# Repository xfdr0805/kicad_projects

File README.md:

# kicad_projects
kicad_projects

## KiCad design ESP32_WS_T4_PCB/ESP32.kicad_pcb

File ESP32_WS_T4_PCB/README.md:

# ESP32_WS_T4_PCB
2021.07.07 从LCEDA导出，放弃LCEDA

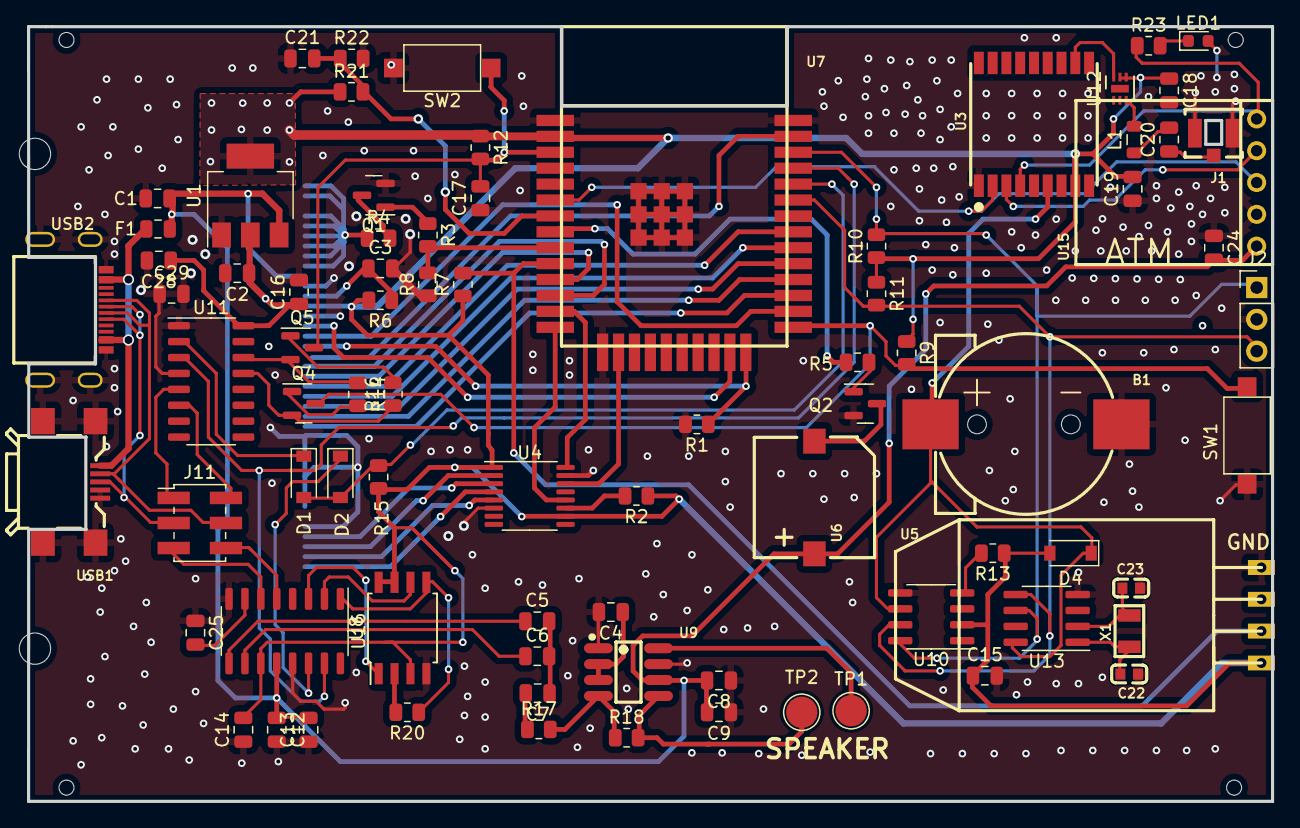
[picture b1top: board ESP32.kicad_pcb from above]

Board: 2 copper layers, 99.3 x 61.8 mm, 83 parts (0 on the bottom side), 76 nets.

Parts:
B1: CR1220-2; BAT-SMD_CR1220-2
C1, C2, C3, C9: 10uF; C_0805_2012Metric
C4, C5, C6, C8, C12, C14, C15, C17, C25, C28: 1uF; C_0805_2012Metric
C7: 0.15uF; C_0805_2012Metric
C13, C16, C18, C19, C24, C29: 0.1uF; C_0805_2012Metric
C20: 100pF; C_0805_2012Metric
C21: 100nF; C_0805_2012Metric
C22, C23: 22pF; C0603
D1, D2, D4: 1N4148WT1G; D_SOD-123
F1: 5V 500mA; Fuse_0805_2012Metric
J1: ANT; IPEX
J2: I2C; PinHeader_1x03_P2.54mm_Vertical
J11: 2mm_2x3; PinHeader_2x03_P2.00mm_Vertical_SMD
L1: 6.8nH; L_0805_2012Metric
LED1: led Green; LED_0603_1608Metric
Q1, Q2, Q4, Q5: S8050; SOT-23
R1, R2, R3, R5, R7, R8, R9, R10, R11, R21, R22: 4.7k; R_0805_2012Metric
R4: 0; R_0805_2012Metric
R6, R12, R13, R14, R16, R17: 10k; R_0805_2012Metric
R15, R23: 1k; R_0805_2012Metric
R18: 33k; R_0805_2012Metric
R20: 100; R_0805_2012Metric
SW1: Download; SW_SPST_CK_RS282G05A3
SW2: Reset; SW_SPST_CK_RS282G05A3
TFT1: TFT_39Pin_4.0; TFT_39PIN_4.0
TP1: TestPoint; TestPoint_Pad_D2.5mm
TP2: SPEAKER; TestPoint_Pad_D2.5mm
U1: UOT; SOT-223
U3: ATGM336H-5N31; GPSM-SMD_ATGM336H
U4: XPT2046; TSSOP-16_4.4x5mm_P0.65mm
U5: GND; DHT22_AM2303
U6: 无源蜂鸣器; BUZ-SMD_2PIN_FST-9650B-5V
U7: 32D; ESP32-WROOM-32D
U8: GD25Q32CSIG; SOIC-8W_5.3x5.3mm_P1.27mm
U9: 8002A; SOP8150MIL-LJN
U10: DS3231MZ+; SOIC-8_3.9x4.9mm_P1.27mm
U11: CH340C; SO-16_3.9x9.9mm_P1.27mm
U12: AT2659; DFN-6-1EP_2x2mm_P0.5mm_EP0.61x1.42mm
U13: PCF8563T/5,518; SOIC-8_3.9x4.9mm_P1.27mm
U15: ATM; GOOUUU-GPS+BD
U16: BY5301; SO-16_3.9x9.9mm_P1.27mm
USB1: MICRO CBJB1.17-4P; MICRO-USB
USB2: TYPE-C-31-M-13; USB-C-SMD_TYPE-C-31-M-13
X1: 32.768KHz; OSC-SMD_L3.2-W1.5

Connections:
+3V3: C2.1, C14.2, C15.1, C16.1, C18.1, C19.2, C28.1, D4.2 (A), R2.1, R6.2, R7.1, R9.1, R10.1, R11.1, R12.1, R13.1, R15.1, R21.1, TFT1.27 (VCC), U1.2 (OUT), U1.4 (1), U3.8 (VCC), U4.1 (VCC), U4.10 (IOVDD), U5.1, U7.2 (3V3), U8.3 (WP#), U8.7 (HOLD#), U8.8 (VCC), U10.2 (VCC), U11.16 (VCC), U12.4 (VDD), U12.5 (/SHDN), U16.11 (V3V)
/1PPS: R23.1, U3.4 (1PPS), U15.5 (PPS)
/ADC1_CH7: C21.2, R21.2, R22.1, U7.7 (IO35)
/BEEP: R5.2, U7.8 (IO32)
/CH340_RX: U7.35 (TXD0), U11.3 (RXD), U16.15 (RX)
/CH340_TX: D1.1 (K), U11.2 (TXD)
/DAC_L: C5.1, U16.9 (DACL)
/DAC_R: C6.1, U16.10 (DACR)
/DHT_DATA: R7.2, U5.2, U7.10 (IO25)
/EN: C17.2, Q5.3 (C), R12.2, SW2.1, U7.3 (EN)
/ESP32_RX: D1.2 (A), D2.2 (A), R15.2, U7.34 (RXD0)
/GPIO_0: Q4.3 (C), R9.2, SW1.1, U7.25 (IO0)
/GPS_RX: U3.3 (RXD), U15.4 (RXD)
/GPS_TX: U3.2 (TXD), U7.6 (IO34), U15.3 (TXD)
/IRQ: R2.2, U4.11 (PENIRQ#)
/SCL: J2.1, R10.2, U7.36 (IO22), U10.8 (SCL), U13.6 (SCL)
/SDA: J2.3, R11.2, U7.33 (IO21), U10.7 (SDA), U13.5 (SDA)
/TFT_BL: R3.2, R8.2, U7.9 (IO33)
/TFT_D0: TFT1.22 (DB0), U7.37 (IO23)
/TFT_D1: TFT1.21 (DB1), U7.12 (IO27)
/TFT_D2: TFT1.20 (DB2), U7.11 (IO26)
/TFT_D3: TFT1.19 (DB3), U7.31 (IO19)
/TFT_D4: TFT1.18 (DB4), U7.30 (IO18)
/TFT_D5: TFT1.17 (DB5), U7.29 (IO5)
/TFT_D6: TFT1.16 (DB6), U7.28 (IO17)
/TFT_D7: TFT1.15 (DB7), U7.27 (IO16)
/TFT_DC: TFT1.25 (RS), U7.23 (IO15)
/TFT_RD: R1.1, TFT1.23 (RD), U7.24 (IO2)
/TFT_WR: TFT1.24 (WR), U7.26 (IO4)
/TOUCH_MISO: U4.12 (DOUT), U7.14 (IO12)
/TOUCH_MOSI: U4.14 (DIN), U7.16 (IO13)
/TOUCH_SCK: U4.16 (DCLK), U7.13 (IO14)
/USB_DM: J11.6, U16.5 (DM)
/USB_DP: J11.5, U16.6 (DP)
/V-BAT: B1.1, D4.1 (K), U3.6 (VBAT), U10.6 (VBAT), U13.8 (VDD)
/VCC_5V: C1.1, C8.2, C9.2, C12.1, C13.2, C24.2, F1.2, TFT1.30 (A), U1.3 (IN), U6.1 (+), U9.6 (VDD), U15.1 (VCC), U16.12 (DC5V)
/VOICE_CS: U8.1 (CS#), U16.3 (SPI_CS)
/VOICE_DO: R20.1, U8.5 (SI), U16.1 (SPI_DO)
/VOICE_SCK: U8.6 (SCLK), U16.2 (SPI_CLK)
/VOICE_TX: D2.1 (K), U16.14 (TX)
/X+: TFT1.3 (XR), U4.2 (XP)
/X-: TFT1.1 (XL), U4.4 (XN)
/Y+: TFT1.4 (YD), U4.3 (YP)
/Y-: TFT1.2 (YU), U4.5 (YN)
GND: B1.2, C1.2, C2.2, C3.2, C4.2, C8.1, C9.1, C12.2, C13.1, C14.1, C15.2, C16.2, C17.1, C18.2, C19.1, C21.1, C22.2, C23.2, C24.1, C25.1, C28.2, C29.1, C29.2, J1.2, J1.3, J2.2, LED1.2 (K), Q1.2 (E), Q2.2 (E), R1.2, R8.1, R22.2, SW1.2, SW2.2, TFT1.5 (GND), TFT1.7 (DB15), TFT1.8 (DB14), TFT1.9 (DB13), TFT1.10 (DB12), TFT1.11 (DB11), TFT1.12 (DB10), TFT1.13 (DB9), TFT1.14 (DB8), TFT1.26 (CS), TFT1.29 (GND), U1.1 (GND), U3.1 (GND), U4.6 (GND), U4.15 (CS#), U5.4, U7.1 (GND), U7.15 (GND), U7.38 (GND), U7.39 (GND), U8.4 (VSS), U9.1 (SHUTDOWN), U9.7 (GND), U10.5 (GND), U11.1 (GND), U12.1 (GND), U12.2 (GND), U13.4 (VSS), U15.2 (GND), U16.8 (GND), U16.13 (GND), USB1.4 (ID), USB1.5 (GND), USB1.6 (EH), USB2.0 (EP), USB2.A1 (GND), USB2.A12 (GND), USB2.B1 (GND), USB2.B12 (GND)
unnamed: C3.1, R6.1, TFT1.28 (RST)
unnamed: C4.1, U9.2 (BYPASS), U9.3 (+IN)
unnamed: C5.2, C6.2, C7.1
unnamed: C7.2, R17.1
unnamed: C20.1, J1.1
unnamed: C20.2, L1.1
unnamed: C22.1, U13.1 (OSCI), X1.2 (OSC2)
unnamed: C23.1, U13.2 (OSCO), X1.1 (OSC1)
unnamed: C25.2, U16.7 (VPN)
unnamed: F1.1, USB1.1 (VCC), USB2.A4 (VBUS), USB2.A9 (VBUS), USB2.B4 (VBUS), USB2.B9 (VBUS)
unnamed: J11.1, U11.5 (D+)
unnamed: J11.2, U11.6 (D-)
unnamed: J11.3, USB1.3 (D+), USB2.A6 (DP1), USB2.B6 (DP2)
unnamed: J11.4, USB1.2 (D-), USB2.A7 (DN1), USB2.B7 (DN2)
unnamed: L1.2, U12.3 (RFIN)
unnamed: LED1.1 (A), R23.2
unnamed: Q1.1 (B), R3.1
unnamed: Q1.3 (C), R4.2
unnamed: Q2.1 (B), R5.1
unnamed: Q2.3 (C), U6.2 (-)
unnamed: Q4.1 (B), R14.2
unnamed: Q4.2 (E), R16.1, U11.13 (DTR#)
unnamed: Q5.1 (B), R16.2
unnamed: Q5.2 (E), R14.1, U11.14 (RTS#)
unnamed: R4.1, TFT1.31 (K1), TFT1.32 (K2), TFT1.33 (K3), TFT1.34 (K4), TFT1.35 (K5), TFT1.36 (K6), TFT1.38 (K7), TFT1.39 (K8)
unnamed: R13.2, U10.4 (RST#)
unnamed: R17.2, R18.1, U9.4 (-IN)
unnamed: R18.2, TP2.1, U9.5 (VO1)
unnamed: R20.2, U8.2 (SO)
unnamed: TP1.1, U9.8 (VO2)
unnamed: U3.11 (RF_IN), U12.6 (RFOUT)

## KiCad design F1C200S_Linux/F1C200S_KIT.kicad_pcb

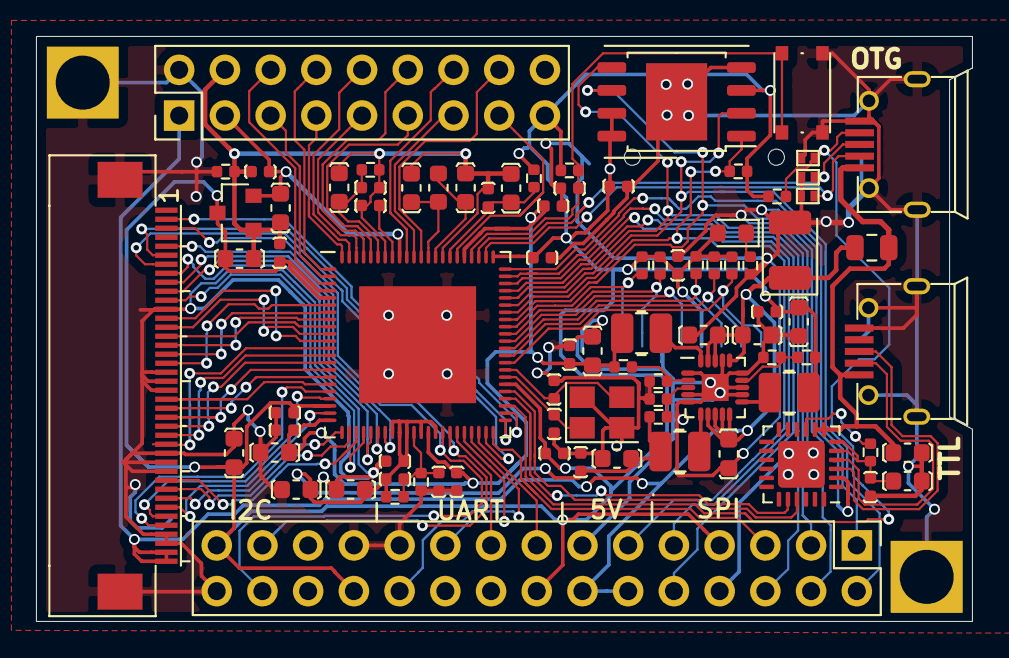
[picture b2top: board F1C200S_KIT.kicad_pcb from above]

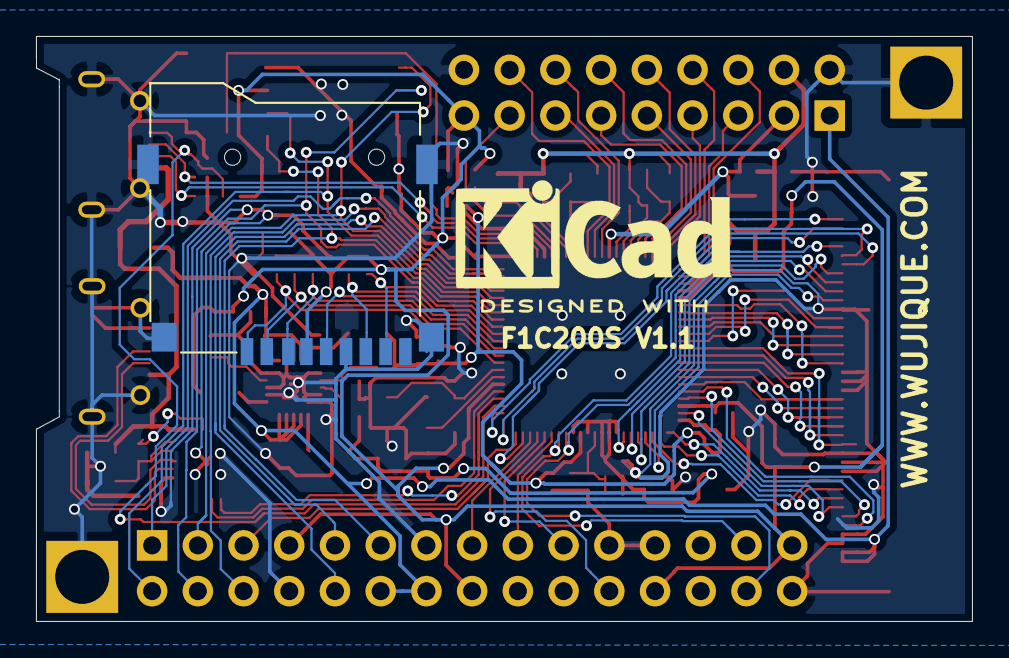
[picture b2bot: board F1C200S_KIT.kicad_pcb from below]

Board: 2 copper layers, 52.0 x 32.5 mm, 89 parts (2 on the bottom side), 91 nets.

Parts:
C1, C2, C5, C11, C12, C19, C21, C22, C23, C27, C28, C29, C41: 03.4004_C0603_10uF; C_0603_WJQ
C3, C4, C6, C7, C8, C9, C10, C13, C14, C15, C20, C24, C25, C26, C34, C36, C37, C40, C42: 03.0009_C0402_100nF; C_0402_WJQ
C16, C38: 03.0001_C0402_1uF; C_0402_WJQ
C17, C18: 03.0003_C0402_10pF; C_0402_WJQ
C30: 04.0002_CP1210_47uF; CP_EIA-3528-21_Kemet-B
C31: 03.4001_C0603_1uF; C_0603_WJQ
C33: 03.4002_C0603_2.2uF; C_0603_WJQ
C39, C43, C45: 03.4003_C0603_4.7uF; C_0603_WJQ
C44: 03.0016_C0603_10uF; C_0603_1608Metric
D1: 07.0201_LED_Red_0603; LED_0603_1608Metric
D3, D4, D5: 07.0002_D_TVS_PESDNC2FD5VB; DFN1006-2L
F1: 07.0004_Fuse_0805_500mA; Fuse_0805_2012Metric
H1, H2: MountingHole_Pad_M3; MP_HOLE_L4_M3
J1: 10.0402_LCD_RGB_CON_WJQ; FPC_40_0.5_BR
J2, J5: 10.0002_USB_Micro; MicroUSB_5S_B_A01SB141B1-067
J3: 10.0001_Micro_SD_Card; microSD_HRO_TF_01A
J4: 10.0201_PH2X15_2D54_V; PinHeader_2x15_P2.54mm_Vertical
J6: 10.0202_PH2X9_2D54_V; PinHeader_2x09_P2.54mm_Vertical
L1, L2, L3: 06.0102_L2520_2.2uH; L_1008_2520_WJQ
LOGO1: Logo_Open_Hardware_Small; KiCad-Logo2_6mm_SilkScreen
R1, R2, R3, R6, R7, R10, R11, R13, R14, R15, R16, R17, R18, R19, R20, R21, R22: R_US; R_0402_WJQ
R4: 02.0003_R0402_1K_1%; R_0402_WJQ
R5: 02.0001_R0402_0R_1%; R_0402_WJQ
R8: 02.0023_R0402_150K_1%; R_0402_WJQ
R9: 02.0025_R0402_680K_1%; R_0402_WJQ
SW1: 11.0101_SW-A03-08; SW_Push_Button__A03-08
U1: 08.0001_F1C200S; QFN-88_EP_10x10_Pitch0.4mm
U2: 09.0103_XC6206; SOT-23
U3: 09.0102_EA3036; QFN-20_EP_3x3_Pitch0.4mm
U4: 09.0001_CP2104; QFN-24-1EP_4x4mm_P0.5mm_EP2.6x2.6mm
U5: 09.0303_GD5F1GQ4; WSON-8-1EP_8x6mm_P1.27mm_EP3.4x4.3mm
U6: 09.0302_W25Q128JVS; SOIC-8_5.23x5.23mm_P1.27mm
Y1: 07.0403_Crystal_24M_3225; Crystal_SMD_3225-4Pin_3.2x2.5mm

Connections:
+1V2: C2.1, C4.1, C7.1, C10.1, C23.1, C26.1, L3.1, R11.2, U1.22 (VDD_CORE), U1.35 (VDD_CORE), U1.71 (VDD_CORE)
+2V5: C11.1, C12.1, C13.1, C14.2, C22.1, C25.1, L2.1, R1.2, R10.2, U1.30 (VCC_DRAM), U1.31 (VCC_DRAM), U1.32 (VCC_DRAM), U1.34 (VCC_DRAM), U1.36 (VCC_DRAM)
+3V3: C1.1, C3.1, C5.1, C6.1, C8.1, C9.1, C21.1, C24.1, C36.1, C37.1, D1.2 (A), J3.4 (VDD), J4.7, J4.16, J4.24, J4.29, J6.17, L1.1, R3.2, R9.1, R13.1, R14.1, R15.1, R16.1, R17.1, R19.2, R20.1, U1.4 (HPVCC), U1.5 (VCC_IO), U1.20 (VCC_IO), U1.50 (VCC_IO), U1.67 (VCC_USB), U2.3 (VI), U5.3 (WP), U5.7 (HOLD), U5.8 (VCC), U6.3 (IO2), U6.7 (IO3), U6.8 (VCC)
+5V: C27.1, C28.1, C29.1, C30.1, F1.1, J1.39 (VCC5V), J1.40 (VCC5V), J4.12, J4.14, J6.1, U3.7 (VIN2), U3.8 (EN2), U3.9 (EN1), U3.10 (VIN1), U3.16 (VCC), U3.18 (EN3), U3.19 (VIN3)
/CPU/CPU_RXD: U1.49 (PE0), U4.21 (TXD)
/CPU/CPU_TXD: U1.48 (PE1), U4.20 (RXD)
/CPU/CTP_INT: J1.2 (CTP_INT), U1.46 (PE3)
/CPU/CTP_RST: J1.6 (CTP_RST), U1.45 (PE4)
/CPU/CTP_SCL: J1.3 (CTP_SCK), J4.27, U1.38 (PE11)
/CPU/CTP_SDA: J1.5 (CTP_SDA), J4.28, U1.37 (PE12/DA_MCLK/TWIO_SDA/PWM0)
/CPU/FMINL: J6.11, U1.84 (FMINL)
/CPU/FMINR: J6.12, U1.85 (FMINR)
/CPU/HP_COM: J6.6, U1.3 (HPCOM)
/CPU/HP_COMFB: J6.5, U1.2 (HPCOMFB)
/CPU/HP_L: J6.8, U1.1 (HPL)
/CPU/HP_R: J6.7, U1.88 (HPR)
/CPU/LCD_BL: J1.7 (LCD_BL), U1.43 (PE6)
/CPU/LCD_CLK: J1.11 (SCK), U1.26 (PD18/LCD_CLK)
/CPU/LCD_D2: J1.18 (B2), U1.6 (PD0/LCD_D2)
/CPU/LCD_D3: J1.17 (B3), U1.7 (PD1/LCD_d3)
/CPU/LCD_D4: J1.16 (B4), U1.8 (PD2/LCD_D4)
/CPU/LCD_D5: J1.15 (B5), U1.9 (PD3/LCD_D5)
/CPU/LCD_D6: J1.14 (B6), U1.10 (PD4/LCD_D6)
/CPU/LCD_D7: J1.13 (B7), U1.11 (PD5/LCD_D7)
/CPU/LCD_D10: J1.27 (G2), U1.12 (PD6/LCD_D10)
/CPU/LCD_D11: J1.26 (G3), U1.13 (PD7/LCD_D11)
/CPU/LCD_D12: J1.25 (G4), U1.14 (PD8/LCD_D12)
/CPU/LCD_D13: J1.24 (G5), U1.15 (PD9/LCD_D13)
/CPU/LCD_D14: J1.23 (G6), U1.16 (PD10/LCD_D14)
/CPU/LCD_D15: J1.22 (G7), U1.17 (PD11/LCD_D15)
/CPU/LCD_D18: J1.36 (R2), U1.18 (PD12/LCD_D18)
/CPU/LCD_D19: J1.35 (R3), U1.19 (PD13/LCD_D19)
/CPU/LCD_D20: J1.34 (R4), U1.21 (PD14/LCD_D20)
/CPU/LCD_D21: J1.33 (R5), U1.23 (PD15/LCD_D21)
/CPU/LCD_D22: J1.32 (R6), U1.24 (PD16/LCD_D22)
/CPU/LCD_D23: J1.31 (R7), U1.25 (PD17/LCD_D23)
/CPU/LCD_DE: J1.8 (DE), U1.27 (PD19/LCD_DE)
/CPU/LCD_HS: J1.10 (HS), U1.28 (PD20/LCD_HSYNC)
/CPU/LCD_VS: J1.9 (VS), U1.29 (PD21/LCD_VSYNC)
/CPU/LINL: J6.9, U1.86 (LINL)
/CPU/LRADC0: J6.14, U1.79 (LRADC0)
/CPU/MICIN: J6.10, U1.87 (MICIN)
/CPU/PA0_UART1_RTS_SPI1_CS: J4.1, U1.66 (PA0)
/CPU/PA1_UART1_CTS_SPI1_MOSI: J4.6, U1.65 (PA1)
/CPU/PA2_UART1_RX_SPI1_CLK: J4.9, U1.64 (PA2)
/CPU/PA3_UART1_TX_SPI1_MISO: J4.10, U1.63 (PA3)
/CPU/PE5: J4.5, U1.44 (PE5)
/CPU/PE7_UART2_TX_SPI1_CS: J4.15, U1.42 (PE7)
/CPU/PE8_UART2_RX_SPI1_MOSI: J4.22, U1.41 (PE8)
/CPU/PE9_UART2_RTS_SPI1_CLK: J4.19, U1.40 (PE9)
/CPU/PE10_UART2_CTS_SPI1_MISO: J4.17, U1.39 (PE10)
/CPU/SDIO_CLK: J3.5 (CLK), U1.56 (PF2)
/CPU/SDIO_CMD: J3.3 (CMD), R15.2, U1.55 (PF3)
/CPU/SDIO_D0: J3.7 (DAT0), R14.2, U1.57 (PF1)
/CPU/SDIO_D1: J3.8 (DAT1), R13.2, U1.58 (PF0)
/CPU/SDIO_D2: J3.1 (DAT2), R17.2, U1.53 (PF5)
/CPU/SDIO_D3: J3.2 (DAT3/CD), R16.2, U1.54 (PF4)
/CPU/SOCI: C17.1, U1.51 (SOCI), Y1.1
/CPU/SOCO: C18.1, U1.52 (SOCO), Y1.3
/CPU/SPI0_CLK: J4.4, U1.59 (PC0), U5.6 (SCLK), U6.6 (CLK)
/CPU/SPI0_CS: J4.11, R19.1, U1.60 (PC1), U5.1 (CS), U6.1 (~CS)
/CPU/SPI0_MISO: J4.2, U1.61 (PC2), U5.2 (SO), U6.2 (DO(IO1))
/CPU/SPI0_MOSI: J4.3, U1.62 (PC3), U5.5 (SI), U6.5 (DI(IO0))
/CPU/TV_IN0: J6.13, U1.78 (TV_IN0)
/CPU/TV_IN1: J6.16, U1.77 (TV_IN1)
/CPU/TV_OUT: J6.15, U1.72 (TV_OUT)
/CPU/TV_VCC: C41.1, C42.1, U1.73 (TV_VCC)
/CPU/TV_VRN: C44.2, C45.2, U1.75 (TV_VRN)
/CPU/TV_VRP: C43.2, C44.1, U1.76 (TV_VRP)
/CPU/USB_D+: D3.1 (A1), J5.3 (D+), U1.69 (USB+DP)
/CPU/USB_D-: D4.1 (A1), J5.2 (D-), U1.68 (USB_DM)
/CPU/USB_ID: D5.1 (A1), J5.4 (ID), R20.2, U1.47 (PE2)
/CPU/VRA1: C38.1, U1.81 (VRA1)
/CPU/VRA2: C39.1, C40.1, R21.1, U1.83 (VRA2)
/Misc/CP2104_RST: C33.2, C34.2, R18.2, U4.5 (VIO), U4.6 (VDD)
/Misc/VBUS: C31.2, F1.2, J2.1 (VBUS), J5.1 (VBUS), U4.7 (REGIN), U4.8 (VBUS)
GND: C1.2, C2.2, C3.2, C4.2, C6.2, C7.2, C9.2, C10.2, C11.2, C12.2, C13.2, C15.1, C16.2, C17.2, C18.2, C21.2, C22.2, C23.2, C24.2, C25.2, C26.2, C27.2, C28.2, C29.2, C30.2, C31.1, C33.1, C34.1, C36.2, C37.2, D3.2 (A2), D4.2 (A2), D5.2 (A2), H1.1, H2.1, J1.12 (GND), J1.19 (B1), J1.20 (B0), J1.21 (GND), J1.28 (G1), J1.29 (G0), J1.30 (GND), J1.37 (R1), J1.38 (R0), J1.MP (MountPin), J2.5 (GND), J2.6 (Shield), J3.6 (VSS), J3.10 (SHIELD), J4.8, J4.13, J4.21, J4.23, J4.30, J5.5 (GND), J5.6 (Shield), J6.2, J6.18, R2.1, R4.1, R6.1, R7.1, R8.2, SW1.2, U1.89 (EPAD), U3.1 (GND), U3.4 (AGND), U3.5 (GND), U3.12 (GND), U3.13 (AGND), U3.15 (AGND), U3.17 (AGND), U3.21 (PAD), U4.2 (GND), U4.25 (PAD), U5.4 (VSS), U5.9 (EP), U6.4 (GND), Y1.2, Y1.4
GNDA: C5.2, C8.2, C19.2, C20.2, C38.2, C39.2, C40.2, C41.2, C42.2, C43.1, C45.1, J6.4, R5.2, R21.2, U1.74 (TV_GND), U1.82 (AGND), U2.1 (GND)
unnamed: C14.1, C15.2, R1.1, R2.2, U1.33 (SVREF)
unnamed: C16.1, R3.1, SW1.1, U1.70 (RESET)
unnamed: D1.1 (K), R4.2
unnamed: J2.2 (D-), U4.4 (D-)
unnamed: J2.3 (D+), U4.3 (D+)
unnamed: L1.2, U3.11 (SW1)
unnamed: L2.2, U3.6 (SW2)
unnamed: L3.2, U3.20 (SW3)
unnamed: R6.2, R9.2, U3.14 (FB1)
unnamed: R7.2, R10.1, U3.3 (FB2)
unnamed: R8.1, R11.1, U3.2 (FB3)
unnamed: R18.1, U4.9 (~RST)
VDDA: C19.1, C20.1, J6.3, U1.80 (AVCC), U2.2 (VO)

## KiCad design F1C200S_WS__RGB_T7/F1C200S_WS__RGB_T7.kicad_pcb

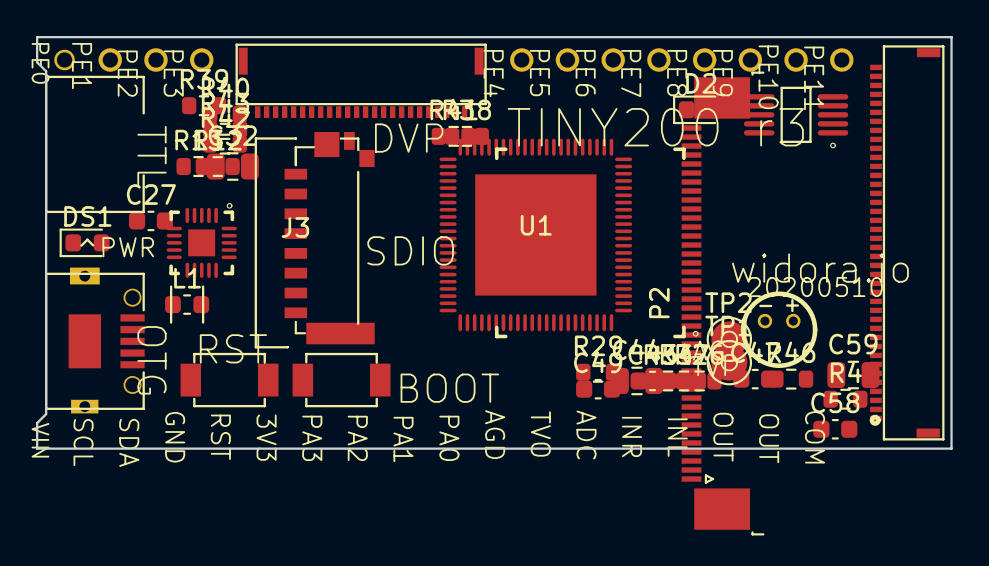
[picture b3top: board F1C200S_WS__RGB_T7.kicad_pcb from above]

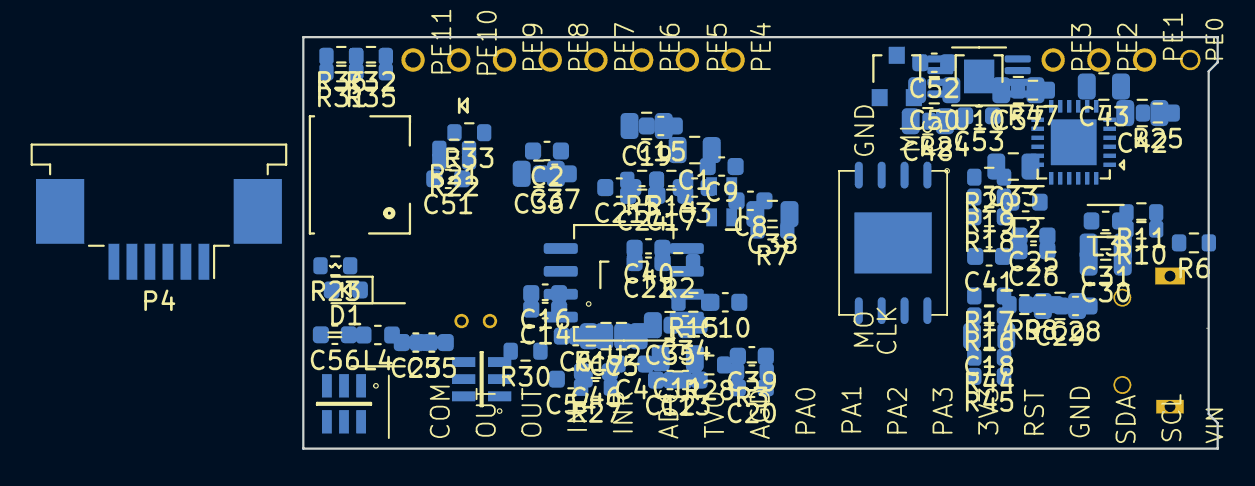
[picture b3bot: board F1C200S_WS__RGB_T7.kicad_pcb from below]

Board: 2 copper layers, 50.8 x 22.9 mm, 136 parts (97 on the bottom side), 88 nets, no tracks yet.

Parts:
C1, C5, C7, C11, C18, C19, C29, C30, C31, C32, C33, C35, C36, C38, C42, C43, C48, C50, C57, C59: 10uF; C_0805_2012Metric
C2, C3, C4, C6, C8, C9, C10, C12, C15, C21, C24, C27, C28, C34, C37, C39, C41, C53, C56, C58: 0.1uF; C_0603_1608Metric
C13, C16, C17, C20, C46, C49, C54, C55: 1uF; C_0603_1608Metric
C14, C22, C23, C40: 4.7uF; C_0603_1608Metric
C25, C26: 10pF; C_0603_1608Metric
C44: 10uF/25V; C_0805_2012Metric
C45: 1nF; C_0603_1608Metric
C47, C51, C52: 104; C_0603_1608Metric
D1, D2: B5819WT; D_0603_1608Metric
DS1: GREEN; LED_0603_1608Metric
J2: MICROUSB-youxin
J3: TF; TF_SLOT
L1, L2, L3, L4: 2.2uH; L_0603_1608Metric
M1: MIC
P1: FFC40-RGBLCD; FFC_SM0.5-1H40
P2: FFC40-RGBLCD; TE_4-1734839-0_1x40-1MP_P0.5mm_Horizontal
P3: Header, 18-Pin; HDR1X18-M2
P4: FPC6; TE_84953-6_1x06-1MP_P1.0mm_Horizontal
R1: 200K; R_0603_1608Metric
R2, R3, R14, R16, R37, R39, R43: 0R; R_0603_1608Metric
R4, R7, R29, R32, R34, R35, R36, R41, R44, R46, R47: 10K; R_0603_1608Metric
R5, R6: 2K/1%; R_0603_1608Metric
R8, R19: 5.1K; R_0603_1608Metric
R9: 680K 1%; R_0603_1608Metric
R10, R13, R15, R18, R28, R30: 150K 1%; R_0603_1608Metric
R11: 470K 1%; R_0603_1608Metric
R12, R17, R21, R23, R31, R33, R38: NC; R_0603_1608Metric
R20, R45: 22R; R_0603_1608Metric
R22, R26: 1K; R_0603_1608Metric
R24: 100K; R_0603_1608Metric
R25, R27: 6R8; R_0603_1608Metric
R40, R42: 75R; R_0603_1608Metric
S1, S2: MINIBUTTON
TP1, TP2: TEST POINT; TestPoint_Pad_D2.0mm
U1: F1C200s; QFN-F1C-89PIN
U2: SPIFLASH_SOP8W; SO-8_5.3x6.2mm_P1.27mm
U3: WSON-SPIFLASH
U4: QFN40P300X300X80_HS-21N
U5, U11: SOT23-6
U6: TSSOP10
U7: QFN24
U8: Header, 24-Pin; FFC_SM0.5-1H24 - OV2640
U9: SOT23
U10: NS2009; MSOP-8-1EP_3x3mm_P0.65mm_EP1.68x1.88mm
X1: XTAL2520

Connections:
/DVP-Y5: R23.2, U1.43 (PE6/CSI_D3/PWM1/DA_OUT/OWA_OUT)
/DVP_DVDD: C56.2, R43.1
/DVP_HSYNC: R12.1, U1.49 (PE0/CSI_HSYNC/TWI2_SCK/UART0_RX)
/DVP_RST: R37.2, R38.1
/DVP_SCL: P4.6, R44.1, U1.18 (PD12/LCD_D18/TWI0_SCK)
/DVP_SDA: P4.5, R46.1, U1.6 (PD0/LCD_D2/TWI0_SDA), U10.9 (SDA)
/DVP_VSYNC: R17.1, U1.48 (PE1/CSI_VSYNC/TWI2_SDA/UART0_TX)
/FMINL: C54.2, U1.84 (FMINL)
/FMINR: C55.2, U1.85 (FMINR)
/HPCOM: R45.1, U1.3 (HPCOM)
/HPCOMFB: C16.1, R45.2, U1.2 (HPCOMFB)
/HPL: R30.2, U1.1 (HPL)
/HPR: R28.2, U1.88 (HPR)
/LCD_CLK: P2.30 (DCLK), U1.26 (PD18/LCD_CLK)
/LCD_D3: P2.24 (B3), U1.7 (PD1/LCD_D3)
/LCD_D4: P2.25 (B4), U1.8 (PD2/LCD_D4)
/LCD_D5: P2.26 (B5), U1.9 (PD3/LCD_D5)
/LCD_D6: P2.27 (B6), U1.10 (PD4/LCD_D6)
/LCD_D7: P2.28 (B7), U1.11 (PD5/LCD_D7)
/LCD_D10: P2.15 (G2), U1.12 (PD6/LCD_D10)
/LCD_D11: P2.16 (G3), U1.13 (PD7/LCD_D11)
/LCD_D12: P2.17 (G4), U1.14 (PD8/LCD_D12)
/LCD_D13: P2.18 (G5), U1.15 (PD9/LCD_D13)
/LCD_D14: P2.19 (G6), U1.16 (PD10/LCD_D14)
/LCD_D15: P2.20 (G7), U1.17 (PD11/LCD_D15)
/LCD_D19: P2.8 (R3), U1.19 (PD13/LCD_D19)
/LCD_D20: P2.9 (R4), U1.21 (PD14/LCD_D20)
/LCD_D21: P2.10 (R5), U1.23 (PD15/LCD_D21)
/LCD_D22: P2.11 (R6), U1.24 (PD16/LCD_D22)
/LCD_D23: P2.12 (R7), U1.25 (PD17/LCD_D23)
/LCD_DE: P2.34 (DE), U1.27 (PD19/LCD_DE)
/LCD_HSYNC: P2.32 (HSYNC), U1.28 (PD20/LCD_HSYNC)
/LCD_VSYNC: P2.33 (VSYNC), U1.29 (PD21/LCD_VSYNC)
/LEDA: P2.2 (LEDA), R20.2
/LEDK: P2.1 (LEDK), R25.2
/LRADC: C45.2, R24.1, U1.79 (LRADC0)
/MICIN: C46.2, U1.87 (MICIN)
/PA0: P4.1, U1.66 (PA0/TPX1/DA_BCLK/UART1_RTS/SPI1_CS)
/PA1: R37.1, U1.65 (PA1/TPX2/DA_LRCK/UART1_CTS/SPI1_MOSI)
/PA2: R14.1, U1.64 (PA2/TPY1/PWM0/DA_IN/UART1_RX/SPI1_CLK)
/PA3: R16.1, U1.63 (PA3/TPY2/IR_RX/DA_OUT/UART1_TX/SPI1_MISO)
/PE12: P4.4, R47.1, U1.37 (PE12/DA_MCLK/TWI0_SDA/PWM0)
/RSTN: C17.1, R4.1, R38.2, U1.70 (~{RESET)
/SDC0_CLK: J3.5 (CLK), U1.56 (PF2/SDC0_CLK/UART0_RX)
/SDC0_CMD: J3.3 (CMD), R34.2, U1.55 (PF3/SDC0_CMD/DBG_DO)
/SDC0_D0: J3.7 (DAT0), R35.2, U1.57 (PF1/SDC0_D0/DBG_DI)
/SDC0_D1: J3.8 (DAT1), R36.2, U1.58 (PF0/SDC0_D1/DBG_MS)
/SDC0_D2: J3.1 (DAT2), R29.2, U1.53 (PF5/SDC0_D2/DBG_CK/PWM1)
/SDC0_D3: J3.2 (CD/DAT3), R32.2, U1.54 (PF4/SDC0_D3/UART0_TX)
/SPI0_CLK: U1.59 (PC0/SPI0_CLK/SDC1_CLK), U2.6 (CLK)
/SPI0_CS: R7.1, U1.60 (PC1/SPI0_CS/SDC1_CMD), U2.1 (/CS)
/SPI0_MISO: U1.61 (PC2/SPI0_MISO/SDC1_D0), U2.2 (DO)
/SPI0_MOSI: U1.62 (PC3/SPI0_MOSI/UART0_TX), U2.5 (DI)
/SVREF: C24.1, C27.2, R5.1, R6.2, U1.33 (SVREF)
/TV_IN0: R40.1, TP1.1, U1.78 (TVIN0)
/TV_OUT: R42.1, U1.72 (TVOUT)
/TV_VRN: C18.1, C23.2, U1.75 (TV_VRN)
/TV_VRP: C18.2, C22.2, U1.76 (TV_VRP)
/VRA1: C13.1, U1.81 (VRA1)
/VRA2: C14.2, C15.2, R1.2, U1.83 (VRA2)
/XI: C26.1, U1.51 (HOSCI)
/XO: C25.2, U1.52 (HOSCO)
AAGND: C53.1, C58.1, C59.2, R39.1
AGND: C5.1, C6.1, C13.2, C14.1, C15.1, C16.2, C22.1, C23.1, C40.1, C41.1, C45.1, C50.2, R1.1, R2.2, R40.2, R42.2, TP2.1, U1.74 (TVGND), U1.82 (AGND)
AVCC: C40.2, C41.2, R22.1, R24.2, U1.80 (AVCC)
AVDD2V8: C53.2, C58.2, C59.1
GND: C1.1, C2.1, C3.1, C4.1, C7.1, C8.1, C9.1, C10.1, C11.1, C12.1, C17.2, C19.1, C20.1, C21.1, C25.1, C26.2, C27.1, C28.1, C29.2, C30.2, C31.2, C32.2, C33.2, C34.1, C35.1, C36.2, C37.1, C38.2, C39.1, C42.2, C43.1, C44.1, C47.2, C48.1, C51.2, C52.1, C56.1, C57.2, J3.6 (VSS), J3.G1 (GND), J3.G2 (GND), J3.G3 (DET1), J3.G4 (DET2), P2.3 (GND), P2.5 (R0), P2.6 (R1), P2.7 (R2), P2.13 (G0), P2.14 (G1), P2.21 (B0), P2.22 (B1), P2.23 (B2), P2.29 (GND), P2.36 (GND), P4.3, R2.1, R6.1, R10.2, R13.2, R18.2, R19.2, R21.2, R25.1, R31.2, R39.2, U1.89 (EPAD), U2.4 (GND), U10.6 (GND), U10.8 (A0)
unnamed: C32.1, R8.1
unnamed: C44.2, R20.1
unnamed: C46.1, R22.2
unnamed: C49.1, R28.1, R30.1
unnamed: C50.1, R27.2
unnamed: P2.35 (NC/PSSEL), R41.2
unnamed: P2.37 (X_R), U10.2 (XP)
unnamed: P2.38 (Y_B), U10.3 (YP)
unnamed: P2.39 (X_L), U10.4 (XN)
unnamed: P2.40 (Y_T), U10.5 (YN)
unnamed: R9.2, R10.1
unnamed: R11.2, R13.1
unnamed: R12.2, R14.2
unnamed: R15.2, R18.1
unnamed: R16.2, R17.2
unnamed: R21.1, R23.1, R26.2
VCC3V3: C1.2, C2.2, C3.2, C4.2, C11.2, C12.2, C28.2, C33.1, C34.2, C47.1, C48.2, C51.1, C52.2, C57.1, J3.4 (VDD), L1.2, P2.4 (VDD), P2.31 (DISP), P4.2, R3.1, R4.2, R7.2, R9.1, R26.1, R29.1, R32.1, R33.2, R34.1, R35.1, R36.1, R41.1, R44.2, R46.2, R47.2, U1.4 (HPVCC), U1.5 (VCC_IO), U1.20 (VCC_IO), U1.50 (VCC_IO), U1.67 (VCC_USB), U2.3 (/WP), U2.7 (/HOLD), U2.8 (VCC), U10.1 (VCC)
VCCIN: C29.1, C30.1, C31.1, C35.2, C42.1, C43.2, L4.1, R27.1
VCC_CORE: C7.2, C8.2, C9.2, C10.2, C38.1, C39.2, L3.2, R15.1, R43.2, U1.22 (VDD_CORE), U1.35 (VDD_CORE), U1.71 (VDD_CORE)
VCC_DRAM: C19.2, C20.2, C21.2, C24.2, C36.1, C37.2, L2.2, R5.2, R11.1, U1.30 (VCC_DRAM), U1.31 (VCC_DRAM), U1.32 (VCC_DRAM), U1.34 (VCC_DRAM), U1.36 (VCC_DRAM)
VCC_TV: C5.2, C6.2, R3.2, U1.73 (TV_VCC)

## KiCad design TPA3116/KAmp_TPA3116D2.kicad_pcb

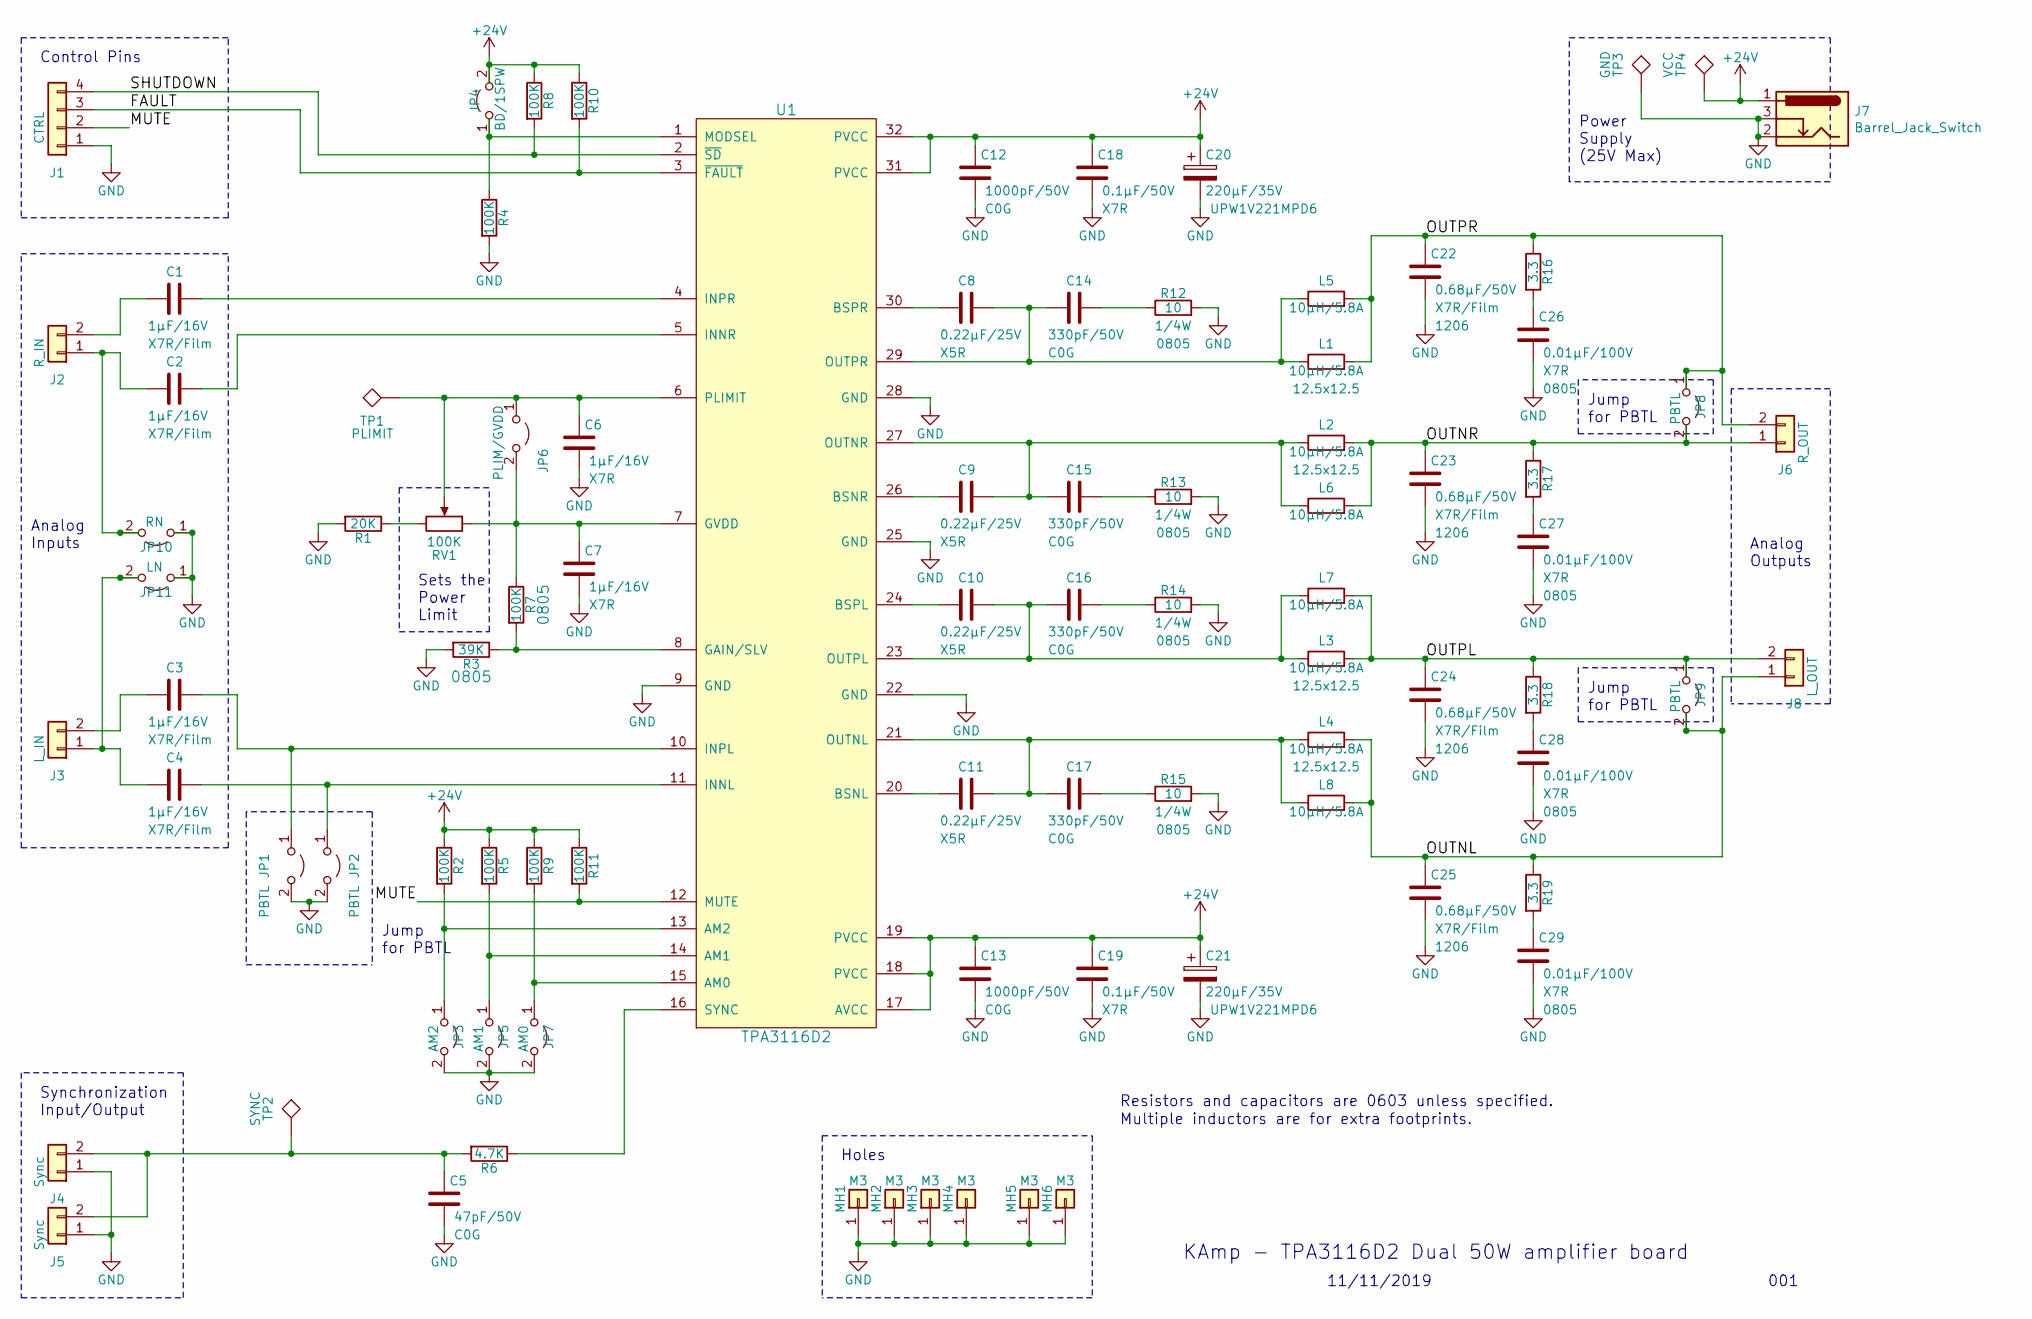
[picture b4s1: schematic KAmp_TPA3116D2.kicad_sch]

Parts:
C1, C2, C3, C4: 1µF/16V; C_0603_1608Metric; Rating X7R/Film
C5: 47pF/50V; C_0603_1608Metric; Rating C0G
C6, C7: 1µF/16V; C_0603_1608Metric; Rating X7R
C8, C9, C10, C11: 0.22µF/25V; C_0603_1608Metric; Rating X5R
C12, C13: 1000pF/50V; C_0603_1608Metric; Rating C0G
C14, C15, C16, C17: 330pF/50V; C_0603_1608Metric; Rating C0G
C18, C19: 0.1µF/50V; C_0603_1608Metric; Rating X7R
C20, C21: 220µF/35V; CP_Radial_D8.0mm_P3.50mm
C22, C23, C24, C25: 0.68µF/50V; C_1206_3216Metric; Rating X7R/Film
C26, C27, C28, C29: 0.01µF/100V; C_0805_2012Metric; Rating X7R
J1: CTRL; Molex_KK-254_AE-6410-04A_1x04_P2.54mm_Vertical
J2: R_IN; Molex_KK-254_AE-6410-02A_1x02_P2.54mm_Vertical
J3: L_IN; Molex_KK-254_AE-6410-02A_1x02_P2.54mm_Vertical
J4, J5: Sync; Molex_KK-254_AE-6410-02A_1x02_P2.54mm_Vertical
J6: R_OUT; PhoenixContact_MSTBA_2,5_2-G_1x02_P5.00mm_Horizontal
J7: Barrel_Jack_Switch; BarrelJack_Horizontal
J8: L_OUT; PhoenixContact_MSTBA_2,5_2-G_1x02_P5.00mm_Horizontal
JP1, JP2: PBTL; PinHeader_1x02_P2.54mm_Vertical
JP3: AM2; R_0603_1608Metric
JP4: BD/1SPW; R_0603_1608Metric
JP5: AM1; R_0603_1608Metric
JP6: PLIM/GVDD; R_0603_1608Metric
JP7: AM0; R_0603_1608Metric
JP8, JP9: PBTL; R_Axial_DIN0204_L3.6mm_D1.6mm_P5.08mm_Horizontal
JP10: RN; R_0603_1608Metric
JP11: LN; R_0603_1608Metric
L1, L2, L3, L4: 10µH/5.8A; L_Bourns_SRR1260
L5, L6, L7, L8: 10µH/5.8A; L_Toroid_Horizontal_D11.2mm_P17.00mm_Diameter12-5mm_Amidon-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
MH1, MH2, MH3, MH4: M3; MountingHole_3mm_Pad_Via
MH5, MH6: M3; MountingHole_3mm_Pad
R1: 20K; R_0603_1608Metric
R2, R4, R5, R7, R8, R9, R10, R11: 100K; R_0603_1608Metric
R3: 39K; R_0603_1608Metric
R6: 4.7K; R_0603_1608Metric
R12, R13, R14, R15: 10; R_0603_1608Metric
R16, R17, R18, R19: 3.3; R_0603_1608Metric
RV1: 100K; Potentiometer_Bourns_3314J_Vertical
TP1: PLIMIT; TestPoint_2Pads_Pitch2.54mm_Drill0.8mm
TP2: SYNC; TestPoint_2Pads_Pitch2.54mm_Drill0.8mm
TP3: GND; TestPoint_2Pads_Pitch2.54mm_Drill0.8mm
TP4: VCC; TestPoint_2Pads_Pitch2.54mm_Drill0.8mm
U1: TPA3116D2; HTSSOP-32-1EP_6.1x11mm_P0.65mm_EP5.2x11mm_Mask4.11x4.36mm_T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

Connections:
+24V: C12.1, C13.1, C18.1, C19.1, C20.1, C21.1, J7.1, JP4.2 (B), R2.1, R5.1, R8.1, R9.1, R10.1, R11.1, TP4.1, U1.17 (AVCC), U1.18 (PVCC), U1.19 (PVCC), U1.31 (PVCC), U1.32 (PVCC)
/FAULT: J1.3, R10.2, U1.3 (~FAULT)
/MUTE: J1.2, R11.2, U1.12 (MUTE)
/OUTNL: C25.1, J8.1, JP9.2 (B), L4.2, L8.2, R19.1
/OUTNR: C23.1, J6.1, JP8.2 (B), L2.2, L6.2, R17.1
/OUTPL: C24.1, J8.2, JP9.1 (A), L3.2, L7.2, R18.1
/OUTPR: C22.1, J6.2, JP8.1 (A), L1.2, L5.2, R16.1
/SHUTDOWN: J1.4, R8.2, U1.2 (~SD)
GND: C5.2, C6.2, C7.2, C12.2, C13.2, C18.2, C19.2, C20.2, C21.2, C22.2, C23.2, C24.2, C25.2, C26.2, C27.2, C28.2, C29.2, J1.1, J4.1, J5.1, J7.2, J7.3, JP1.2 (B), JP2.2 (B), JP3.2 (B), JP5.2 (B), JP7.2 (B), JP10.1 (A), JP11.1 (A), MH1.1, MH2.1, MH3.1, MH4.1, MH5.1, MH6.1, R1.2, R3.2, R4.2, R12.2, R13.2, R14.2, R15.2, TP3.1, U1.9 (GND), U1.22 (GND), U1.25 (GND), U1.28 (GND), U1.33 (GND)
unnamed: C1.1, U1.4 (INPR)
unnamed: C1.2, J2.2
unnamed: C2.1, U1.5 (INNR)
unnamed: C2.2, J2.1, JP10.2 (B)
unnamed: C3.1, JP1.1 (A), U1.10 (INPL)
unnamed: C3.2, J3.2
unnamed: C4.1, JP2.1 (A), U1.11 (INNL)
unnamed: C4.2, J3.1, JP11.2 (B)
unnamed: C5.1, J4.2, J5.2, R6.2, TP2.1
unnamed: C6.1, JP6.1 (A), RV1.2, TP1.1, U1.6 (PLIMIT)
unnamed: C7.1, JP6.2 (B), R7.1, RV1.1, U1.7 (GVDD)
unnamed: C8.2, U1.30 (BSPR)
unnamed: C9.2, U1.26 (BSNR)
unnamed: C10.1, C16.2, L3.1, L7.1, U1.23 (OUTPL)
unnamed: C10.2, U1.24 (BSPL)
unnamed: C11.1, C17.2, L4.1, L8.1, U1.21 (OUTNL)
unnamed: C11.2, U1.20 (BSNL)
unnamed: C14.1, R12.1
unnamed: C8.1, C14.2, L1.1, L5.1, U1.29 (OUTPR)
unnamed: C15.1, R13.1
unnamed: C9.1, C15.2, L2.1, L6.1, U1.27 (OUTNR)
unnamed: C16.1, R14.1
unnamed: C17.1, R15.1
unnamed: C26.1, R16.2
unnamed: C27.1, R17.2
unnamed: C28.1, R18.2
unnamed: C29.1, R19.2
unnamed: JP3.1 (A), R2.2, U1.13 (AM2)
unnamed: JP4.1 (A), R4.1, U1.1 (MODSEL)
unnamed: JP5.1 (A), R5.2, U1.14 (AM1)
unnamed: JP7.1 (A), R9.2, U1.15 (AM0)
unnamed: R1.1, RV1.3
unnamed: R3.1, R7.2, U1.8 (GAIN/SLV)
unnamed: R6.1, U1.16 (SYNC)

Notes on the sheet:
Analog Inputs
Control Pins
Synchronization Input/Output
Jump for PBTL
Sets the Power Limit
Holes
Resistors and capacitors are 0603 unless specified.
Multiple inductors are for extra footprints.
KAmp - TPA3116D2 Dual 50W amplifier board
11/11/2019
Power Supply (25V Max)
Analog Outputs
001

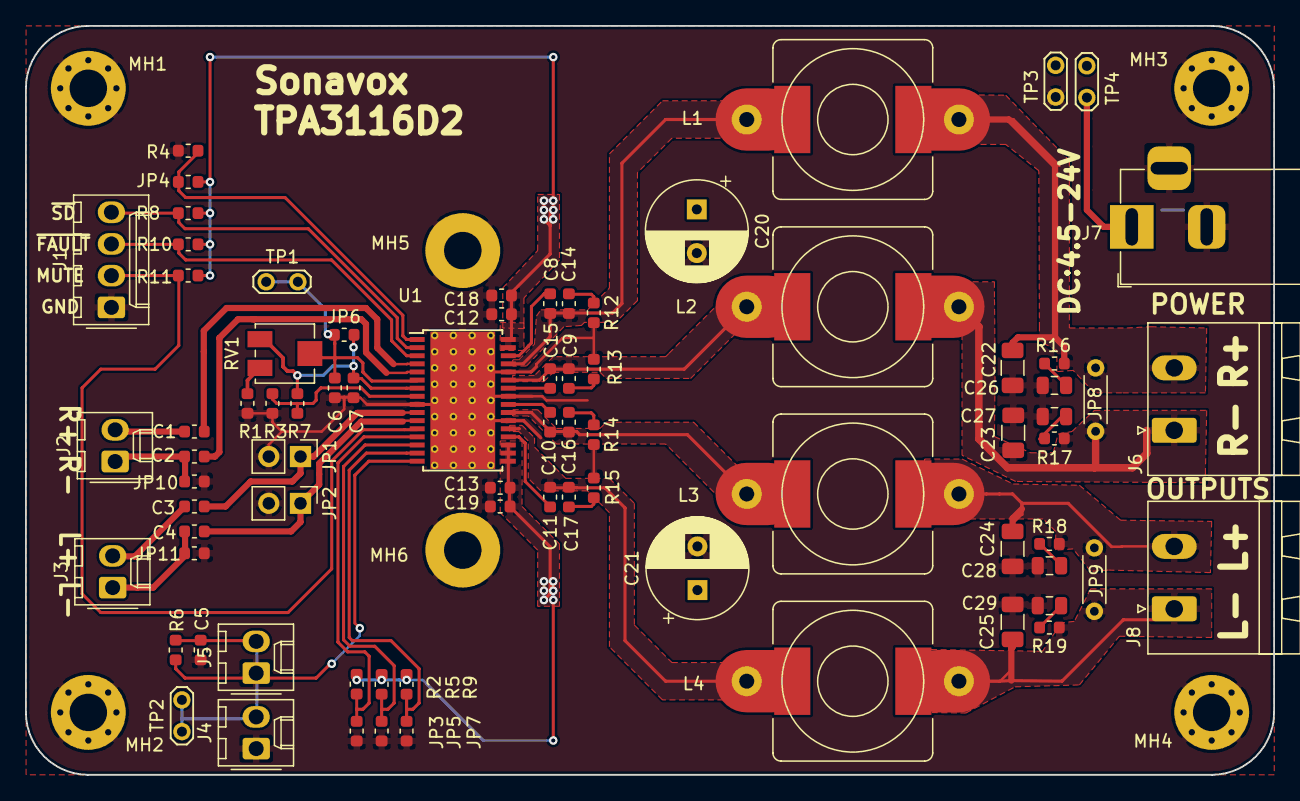
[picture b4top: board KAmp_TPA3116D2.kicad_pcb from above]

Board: 2 copper layers, 100.0 x 60.0 mm, 87 parts (0 on the bottom side), 43 nets.
